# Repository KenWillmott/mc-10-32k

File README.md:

# mc-10-32k
A 32k memory upgrade PCB for the Radio Shack MC-10 microcomputer
This is preliminary information but the circuit has been built and tested on a different board.

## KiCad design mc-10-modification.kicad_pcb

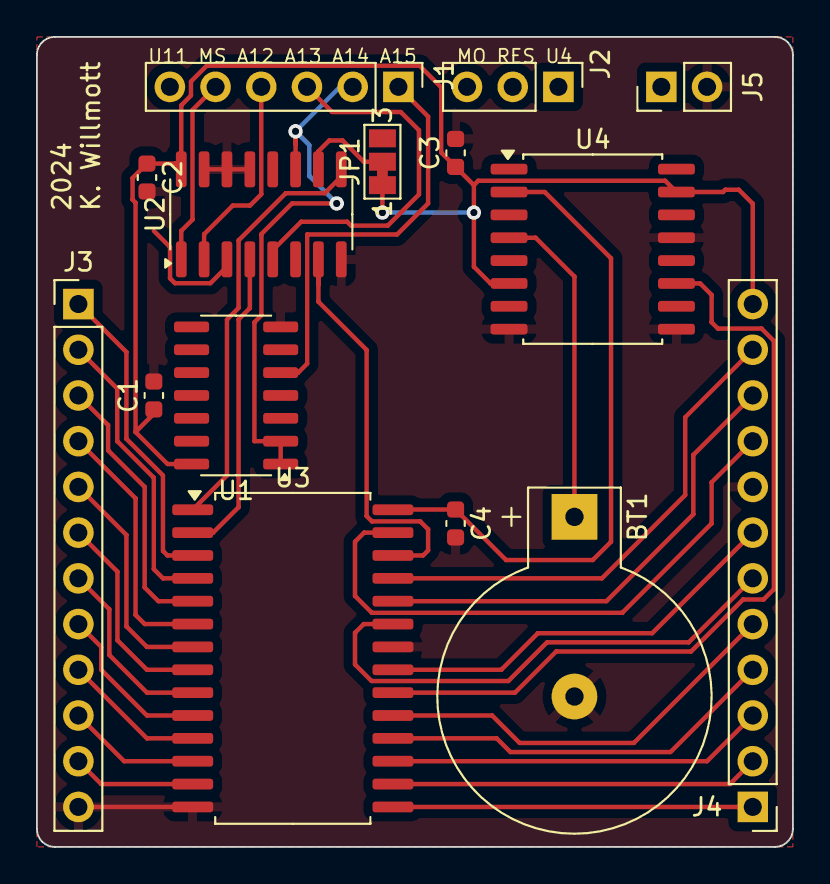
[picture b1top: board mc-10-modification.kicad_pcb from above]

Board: 2 copper layers, 42.0 x 45.0 mm, 15 parts (0 on the bottom side), 38 nets.

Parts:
BT1: 3.0V; BatteryHolder_Keystone_500
C1, C2, C3, C4: 100n; C_0603_1608Metric
J1: Conn_01x06_Pin; PinHeader_1x06_P2.54mm_Vertical
J2: Conn_01x03_Pin; PinHeader_1x03_P2.54mm_Vertical
J3, J4: Conn_01x12; PinHeader_1x12_P2.54mm_Vertical
J5: Conn_01x02_Pin; PinHeader_1x02_P2.54mm_Vertical
JP1: Jumper_3_Bridged12; SolderJumper-3_P1.3mm_Bridged12_Pad1.0x1.5mm_NumberLabels
U1: 74HCT00; SO-14_3.9x8.65mm_P1.27mm
U2: 74HCT157; SOP-16_3.9x9.9mm_P1.27mm
U3: KM62256CLP; SOP-28_8.4x18.16mm_P1.27mm
U4: DS1210S; SOIC-16W_7.5x10.3mm_P1.27mm

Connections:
/A0: J3.8, U3.10 (A0)
/A1: J3.7, U3.9 (A1)
/A2: J3.6, U3.8 (A2)
/A3: J3.5, U3.7 (A3)
/A4: J3.4, U3.6 (A4)
/A5: J3.3, U3.5 (A5)
/A6: J3.2, U3.4 (A6)
/A7: J3.1, U3.3 (A7)
/A8: J4.11, U3.25 (A8)
/A9: J4.10, U3.24 (A9)
/A10: J4.7, U3.21 (A10)
/A11: J4.6, U3.23 (A11)
/D0: J3.9, U3.11 (Q0)
/D1: J3.10, U3.12 (Q1)
/D2: J3.11, U3.13 (Q2)
/D3: J4.1, U3.15 (Q3)
/D4: J4.2, U3.16 (Q4)
/D5: J4.3, U3.17 (Q5)
/D6: J4.4, U3.18 (Q6)
/D7: J4.5, U3.19 (Q7)
/MA12: U2.4 (Za), U3.2 (A12)
/MA13: U2.7 (Zb), U3.26 (A13)
/MA14: U2.9 (Zc), U3.1 (A14)
/NVCC: C4.1, U3.28 (VCC), U4.2 (VCCO)
/PA12: J1.4, U2.2 (I0a)
/PA13: J1.3, U2.5 (I0b)
/PA14: J1.2, U1.1, U1.2, U2.11 (I0c)
/PA14MOD: J2.1, U1.6
/PA15: J1.1, U1.5
/U11-DA12: J1.6, U2.3 (I1a)
/~MS: J1.5, U2.1 (S)
/~WE: J4.9, U3.27 (~WE)
GND: BT1.2 (-), C1.2, C2.2, C3.2, C4.2, J3.12, J4.8, J5.2, JP1.3 (B), U1.7 (GND), U2.6 (I1b), U2.8 (GND), U2.13 (I1d), U2.14 (I0d), U2.15 (E), U3.14 (GND), U3.22 (~OE), U4.8 (GND), U4.9 (~CE), U4.13 (VBAT2)
unnamed: BT1.1 (+), J5.1, U4.4 (VBAT1)
unnamed: JP1.2 (C), U2.10 (I1c)
unnamed: U1.3, U1.4
unnamed: U3.20 (~CS), U4.11 (~CEO)
VCC: C1.1, C2.1, C3.1, J4.12, JP1.1 (A), U1.14 (VCC), U2.16 (VCC), U4.6 (TOL), U4.15 (VCCI)
